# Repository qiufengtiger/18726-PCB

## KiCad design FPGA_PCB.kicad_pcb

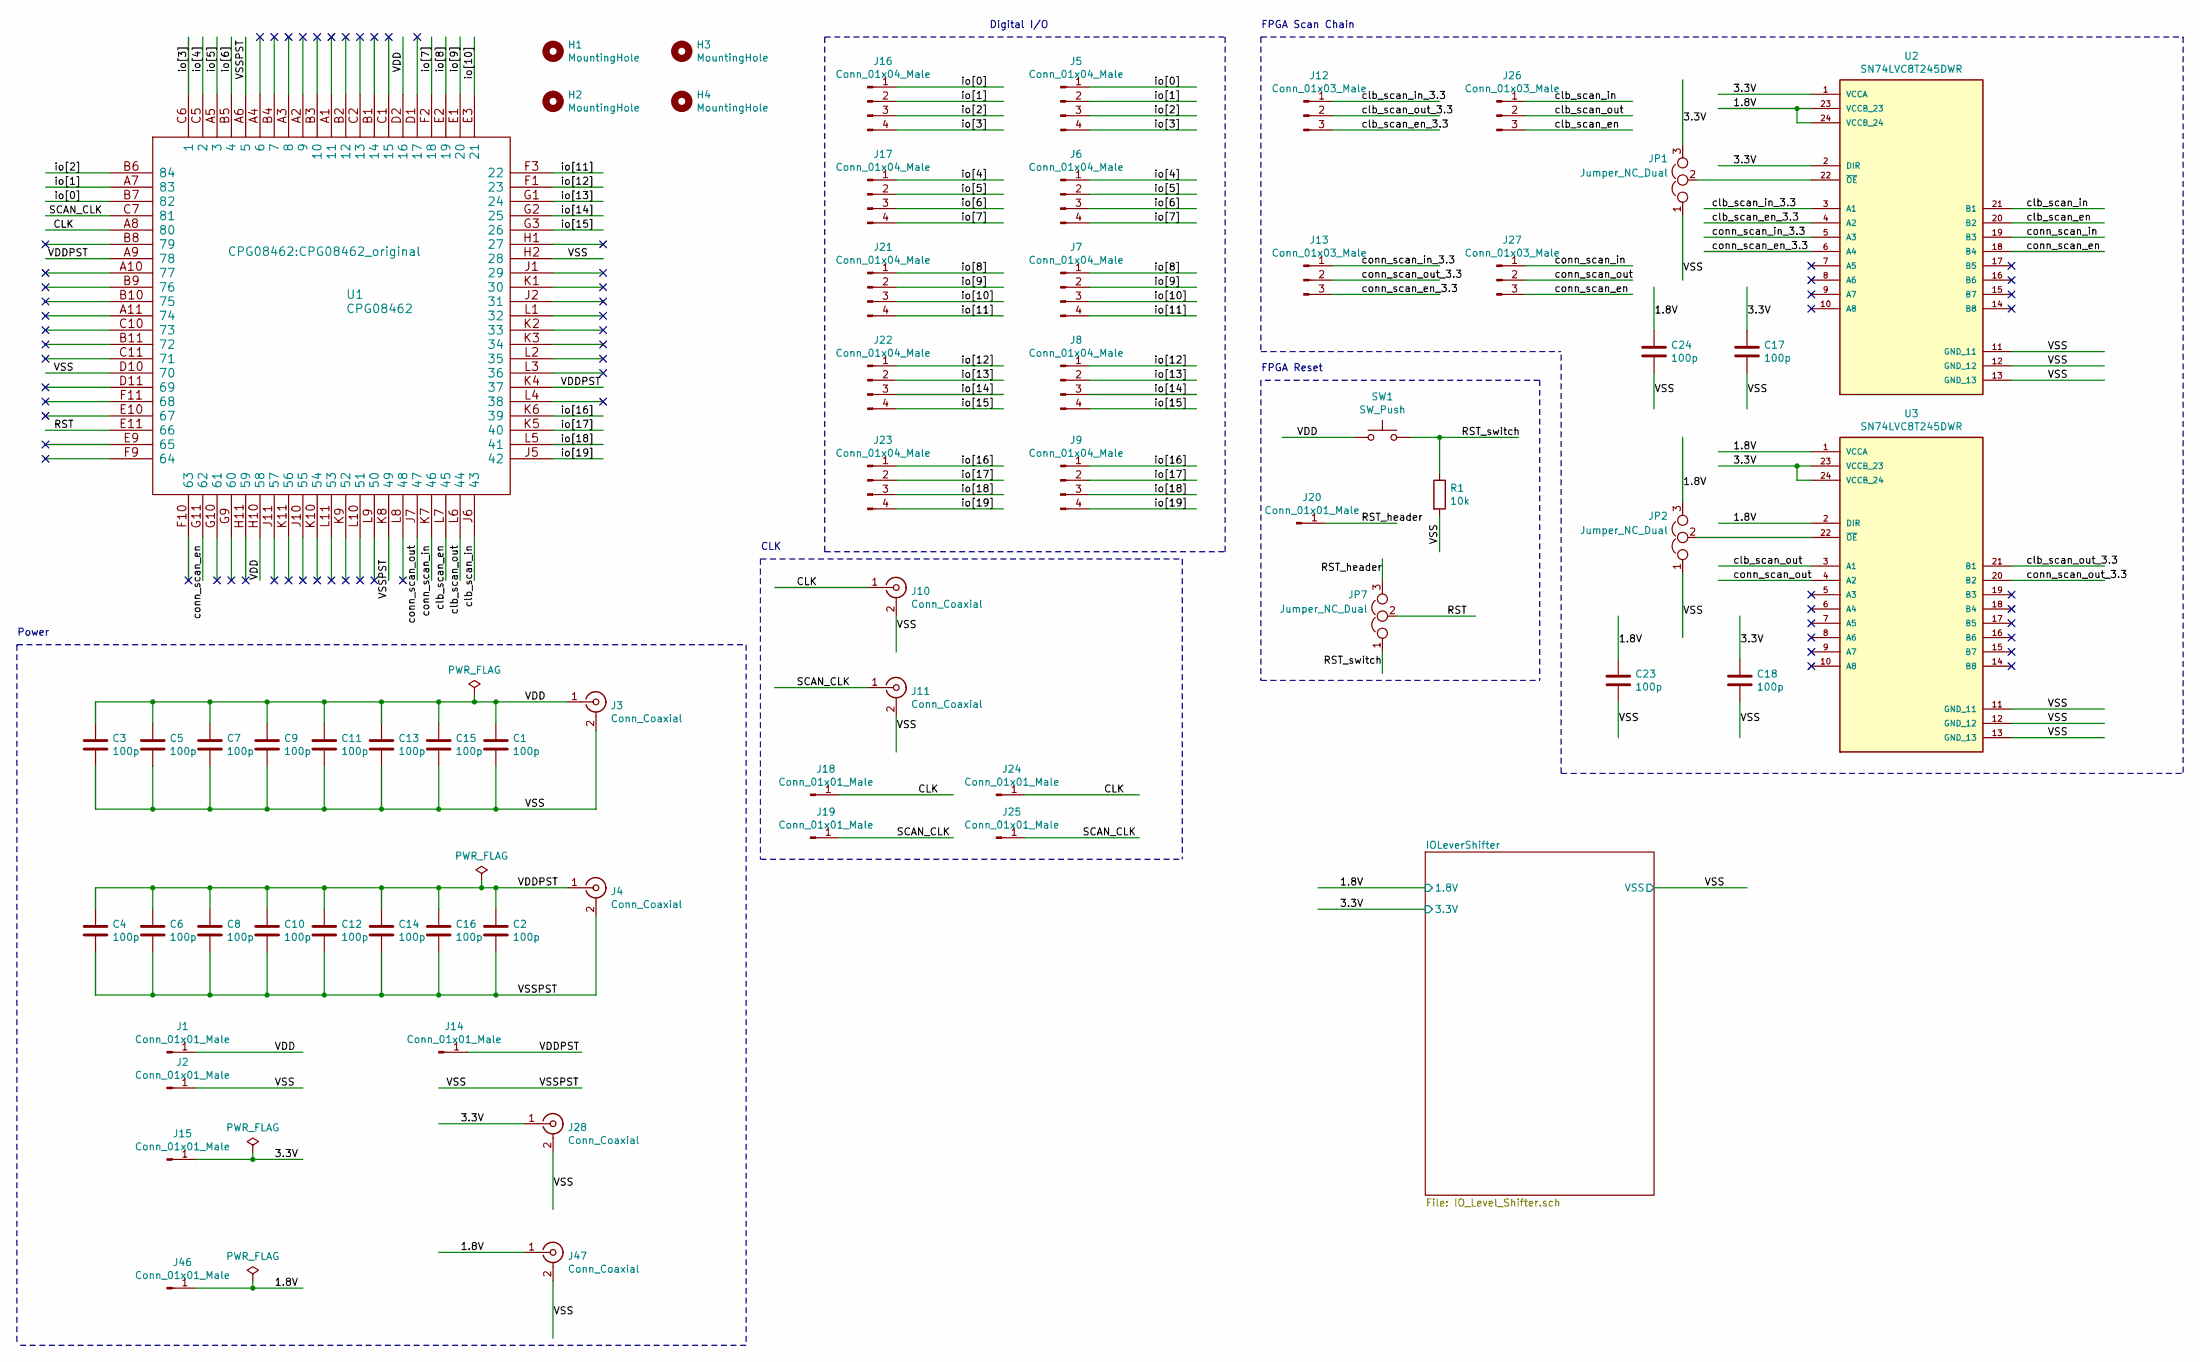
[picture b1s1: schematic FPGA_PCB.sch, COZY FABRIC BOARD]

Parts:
C1, C2, C3, C4, C5, C6, C7, C8, C9, C10, C11, C12, C13, C14, C15, C16, C17, C18, C23, C24: 100p; C_0805_2012Metric_Pad1.15x1.40mm_HandSolder
H1, H2, H3, H4: MountingHole; MountingHole_3.2mm_M3
J1, J2, J14, J15, J18, J19, J20, J24, J25, J46: Conn_01x01_Male; PinHeader_1x01_P2.54mm_Vertical
J3, J4, J10, J11, J28, J47: Conn_Coaxial; BNC_TEConnectivity_1478204_Vertical
J5, J6, J7, J8, J9, J16, J17, J21, J22, J23: Conn_01x04_Male; PinHeader_1x04_P2.54mm_Vertical
J12, J13, J26, J27: Conn_01x03_Male; PinHeader_1x03_P2.54mm_Vertical
JP1, JP2, JP7: Jumper_NC_Dual; PinHeader_1x03_P2.54mm_Vertical
R1: 10k; R_0805_2012Metric_Pad1.15x1.40mm_HandSolder
SW1: SW_Push; SW_SPST_TL3305A
U1: CPG08462; CPG08462_original
U2, U3: SN74LVC8T245DWR; SOIC127P1030X265-24N; PARTREV C

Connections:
/1.8V: C23.1, C24.1, J46.1, J47.1 (In), JP2.3, U2.23 (VCCB_23), U2.24 (VCCB_24), U3.1 (VCCA), U3.2 (DIR); also elsewhere on the board
/3.3V: C17.1, C18.1, J15.1, J28.1 (In), JP1.3, U2.1 (VCCA), U2.2 (DIR), U3.23 (VCCB_23), U3.24 (VCCB_24); also elsewhere on the board
/CLK: J10.1 (In), J18.1, J24.1, U1.A8 (80)
/RST: JP7.2, U1.E11 (66)
/RST_header: J20.1, JP7.3
/RST_switch: JP7.1, R1.1, SW1.2
/SCAN_CLK: J11.1 (In), J19.1, J25.1, U1.C7 (81)
/VDD: C1.1, C3.1, C5.1, C7.1, C9.1, C11.1, C13.1, C15.1, J1.1, J3.1 (In), SW1.1, U1.D2 (16), U1.H10 (58)
/VDDPST: C2.1, C4.1, C6.1, C8.1, C10.1, C12.1, C14.1, C16.1, J4.1 (In), J14.1, U1.A9 (78), U1.K4 (37)
/VSS: C1.2, C2.2, C3.2, C4.2, C5.2, C6.2, C7.2, C8.2, C9.2, C10.2, C11.2, C12.2, C13.2, C14.2, C15.2, C16.2, C17.2, C18.2, C23.2, C24.2, J2.1, J3.2 (Ext), J4.2 (Ext), J10.2 (Ext), J11.2 (Ext), J28.2 (Ext), J47.2 (Ext), JP1.1, JP2.1, R1.2, U1.A6 (5), U1.D10 (70), U1.H2 (28), U1.K8 (49), U2.11 (GND_11), U2.12 (GND_12), U2.13 (GND_13), U3.11 (GND_11), U3.12 (GND_12), U3.13 (GND_13); also elsewhere on the board
/clb_scan_en: J26.3, U1.L7 (45), U2.20 (B2)
/clb_scan_en_3.3: J12.3, U2.4 (A2)
/clb_scan_in: J26.1, U1.J6 (43), U2.21 (B1)
/clb_scan_in_3.3: J12.1, U2.3 (A1)
/clb_scan_out: J26.2, U1.L6 (44), U3.3 (A1)
/clb_scan_out_3.3: J12.2, U3.21 (B1)
/conn_scan_en: J27.3, U1.G11 (62), U2.18 (B4)
/conn_scan_en_3.3: J13.3, U2.6 (A4)
/conn_scan_in: J27.1, U1.K7 (46), U2.19 (B3)
/conn_scan_in_3.3: J13.1, U2.5 (A3)
/conn_scan_out: J27.2, U1.J7 (47), U3.4 (A2)
/conn_scan_out_3.3: J13.2, U3.20 (B2)
/io[0]: J5.1, J16.1, U1.B7 (82)
/io[1]: J5.2, J16.2, U1.A7 (83)
/io[2]: J5.3, J16.3, U1.B6 (84)
/io[3]: J5.4, J16.4, U1.C6 (1)
/io[4]: J6.1, J17.1, U1.C5 (2)
/io[5]: J6.2, J17.2, U1.A5 (3)
/io[6]: J6.3, J17.3, U1.B5 (4)
/io[7]: J6.4, J17.4, U1.F2 (18)
/io[8]: J7.1, J21.1, U1.E2 (19)
/io[9]: J7.2, J21.2, U1.E1 (20)
/io[10]: J7.3, J21.3, U1.E3 (21)
/io[11]: J7.4, J21.4, U1.F3 (22)
/io[12]: J8.1, J22.1, U1.F1 (23)
/io[13]: J8.2, J22.2, U1.G1 (24)
/io[14]: J8.3, J22.3, U1.G2 (25)
/io[15]: J8.4, J22.4, U1.G3 (26)
/io[16]: J9.1, J23.1, U1.K6 (39)
/io[17]: J9.2, J23.2, U1.K5 (40)
/io[18]: J9.3, J23.3, U1.L5 (41)
/io[19]: J9.4, J23.4, U1.J5 (42)
unnamed: JP1.2, U2.22 (~OE)
unnamed: JP2.2, U3.22 (~OE)

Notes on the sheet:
Digital I/O
FPGA Scan Chain
Power
CLK
FPGA Reset

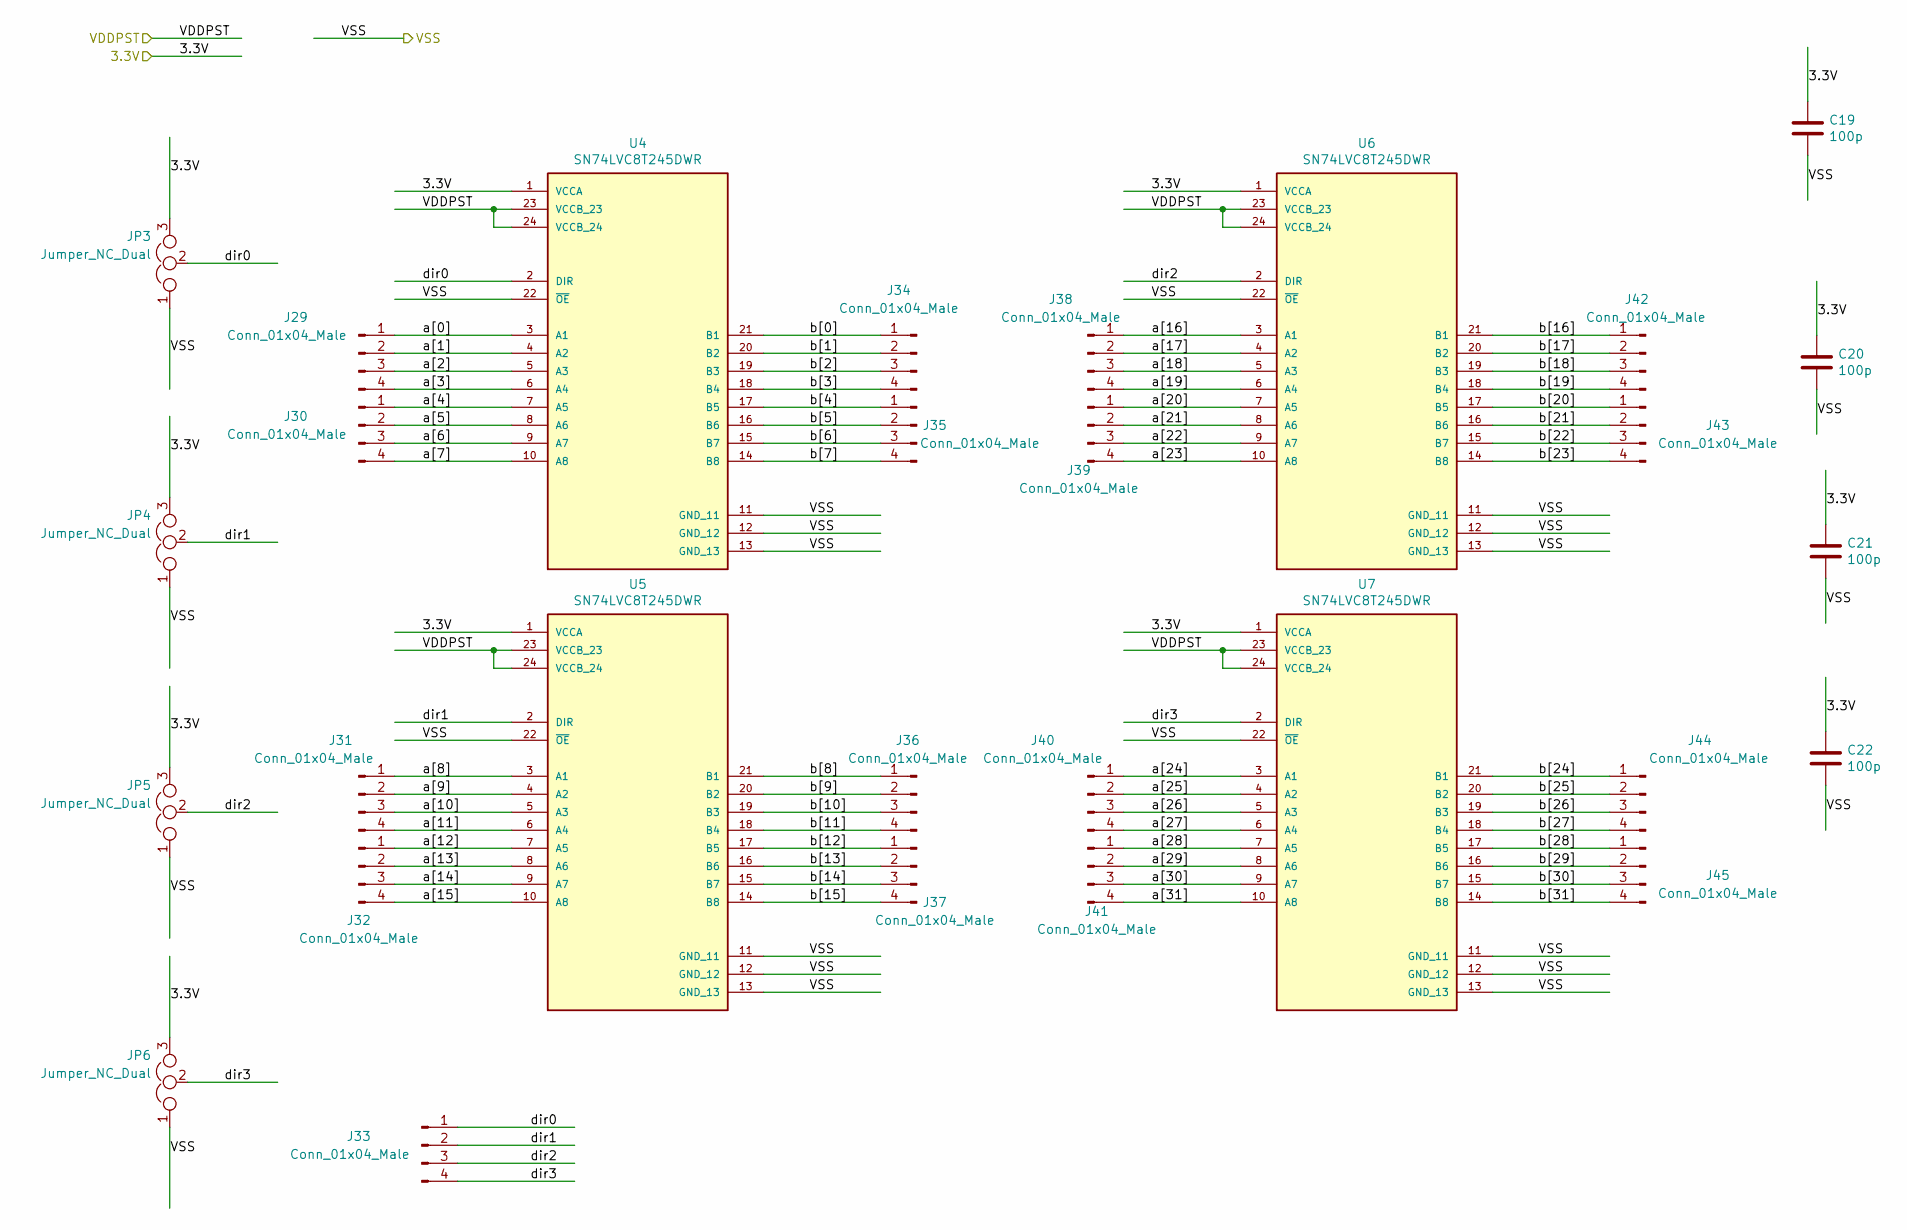
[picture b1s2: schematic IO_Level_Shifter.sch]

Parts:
C19, C20, C21, C22: 100p; C_0805_2012Metric_Pad1.15x1.40mm_HandSolder
J29, J30, J31, J32, J33, J34, J35, J36, J37, J38, J39, J40, J41, J42, J43, J44, J45: Conn_01x04_Male; PinHeader_1x04_P2.54mm_Vertical
JP3, JP4, JP5, JP6: Jumper_NC_Dual; PinHeader_1x03_P2.54mm_Vertical
U4, U5, U6, U7: SN74LVC8T245DWR; SOIC127P1030X265-24N; PARTREV C

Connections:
/1.8V: U4.23 (VCCB_23), U4.24 (VCCB_24), U5.23 (VCCB_23), U5.24 (VCCB_24), U6.23 (VCCB_23), U6.24 (VCCB_24), U7.23 (VCCB_23), U7.24 (VCCB_24); also elsewhere on the board
/3.3V: C19.1, C20.1, C21.1, C22.1, JP3.3, JP4.3, JP5.3, JP6.3, U4.1 (VCCA), U5.1 (VCCA), U6.1 (VCCA), U7.1 (VCCA); also elsewhere on the board
/IOLeverShifter/a[0]: J29.1, U4.3 (A1)
/IOLeverShifter/a[1]: J29.2, U4.4 (A2)
/IOLeverShifter/a[2]: J29.3, U4.5 (A3)
/IOLeverShifter/a[3]: J29.4, U4.6 (A4)
/IOLeverShifter/a[4]: J30.1, U4.7 (A5)
/IOLeverShifter/a[5]: J30.2, U4.8 (A6)
/IOLeverShifter/a[6]: J30.3, U4.9 (A7)
/IOLeverShifter/a[7]: J30.4, U4.10 (A8)
/IOLeverShifter/a[8]: J31.1, U5.3 (A1)
/IOLeverShifter/a[9]: J31.2, U5.4 (A2)
/IOLeverShifter/a[10]: J31.3, U5.5 (A3)
/IOLeverShifter/a[11]: J31.4, U5.6 (A4)
/IOLeverShifter/a[12]: J32.1, U5.7 (A5)
/IOLeverShifter/a[13]: J32.2, U5.8 (A6)
/IOLeverShifter/a[14]: J32.3, U5.9 (A7)
/IOLeverShifter/a[15]: J32.4, U5.10 (A8)
/IOLeverShifter/a[16]: J38.1, U6.3 (A1)
/IOLeverShifter/a[17]: J38.2, U6.4 (A2)
/IOLeverShifter/a[18]: J38.3, U6.5 (A3)
/IOLeverShifter/a[19]: J38.4, U6.6 (A4)
/IOLeverShifter/a[20]: J39.1, U6.7 (A5)
/IOLeverShifter/a[21]: J39.2, U6.8 (A6)
/IOLeverShifter/a[22]: J39.3, U6.9 (A7)
/IOLeverShifter/a[23]: J39.4, U6.10 (A8)
/IOLeverShifter/a[24]: J40.1, U7.3 (A1)
/IOLeverShifter/a[25]: J40.2, U7.4 (A2)
/IOLeverShifter/a[26]: J40.3, U7.5 (A3)
/IOLeverShifter/a[27]: J40.4, U7.6 (A4)
/IOLeverShifter/a[28]: J41.1, U7.7 (A5)
/IOLeverShifter/a[29]: J41.2, U7.8 (A6)
/IOLeverShifter/a[30]: J41.3, U7.9 (A7)
/IOLeverShifter/a[31]: J41.4, U7.10 (A8)
/IOLeverShifter/b[0]: J34.1, U4.21 (B1)
/IOLeverShifter/b[1]: J34.2, U4.20 (B2)
/IOLeverShifter/b[2]: J34.3, U4.19 (B3)
/IOLeverShifter/b[3]: J34.4, U4.18 (B4)
/IOLeverShifter/b[4]: J35.1, U4.17 (B5)
/IOLeverShifter/b[5]: J35.2, U4.16 (B6)
/IOLeverShifter/b[6]: J35.3, U4.15 (B7)
/IOLeverShifter/b[7]: J35.4, U4.14 (B8)
/IOLeverShifter/b[8]: J36.1, U5.21 (B1)
/IOLeverShifter/b[9]: J36.2, U5.20 (B2)
/IOLeverShifter/b[10]: J36.3, U5.19 (B3)
/IOLeverShifter/b[11]: J36.4, U5.18 (B4)
/IOLeverShifter/b[12]: J37.1, U5.17 (B5)
/IOLeverShifter/b[13]: J37.2, U5.16 (B6)
/IOLeverShifter/b[14]: J37.3, U5.15 (B7)
/IOLeverShifter/b[15]: J37.4, U5.14 (B8)
/IOLeverShifter/b[16]: J42.1, U6.21 (B1)
/IOLeverShifter/b[17]: J42.2, U6.20 (B2)
/IOLeverShifter/b[18]: J42.3, U6.19 (B3)
/IOLeverShifter/b[19]: J42.4, U6.18 (B4)
/IOLeverShifter/b[20]: J43.1, U6.17 (B5)
/IOLeverShifter/b[21]: J43.2, U6.16 (B6)
/IOLeverShifter/b[22]: J43.3, U6.15 (B7)
/IOLeverShifter/b[23]: J43.4, U6.14 (B8)
/IOLeverShifter/b[24]: J44.1, U7.21 (B1)
/IOLeverShifter/b[25]: J44.2, U7.20 (B2)
/IOLeverShifter/b[26]: J44.3, U7.19 (B3)
/IOLeverShifter/b[27]: J44.4, U7.18 (B4)
/IOLeverShifter/b[28]: J45.1, U7.17 (B5)
/IOLeverShifter/b[29]: J45.2, U7.16 (B6)
/IOLeverShifter/b[30]: J45.3, U7.15 (B7)
/IOLeverShifter/b[31]: J45.4, U7.14 (B8)
/IOLeverShifter/dir0: J33.1, JP3.2, U4.2 (DIR)
/IOLeverShifter/dir1: J33.2, JP4.2, U5.2 (DIR)
/IOLeverShifter/dir2: J33.3, JP5.2, U6.2 (DIR)
/IOLeverShifter/dir3: J33.4, JP6.2, U7.2 (DIR)
/VSS: C19.2, C20.2, C21.2, C22.2, JP3.1, JP4.1, JP5.1, JP6.1, U4.11 (GND_11), U4.12 (GND_12), U4.13 (GND_13), U4.22 (~OE), U5.11 (GND_11), U5.12 (GND_12), U5.13 (GND_13), U5.22 (~OE), U6.11 (GND_11), U6.12 (GND_12), U6.13 (GND_13), U6.22 (~OE), U7.11 (GND_11), U7.12 (GND_12), U7.13 (GND_13), U7.22 (~OE); also elsewhere on the board

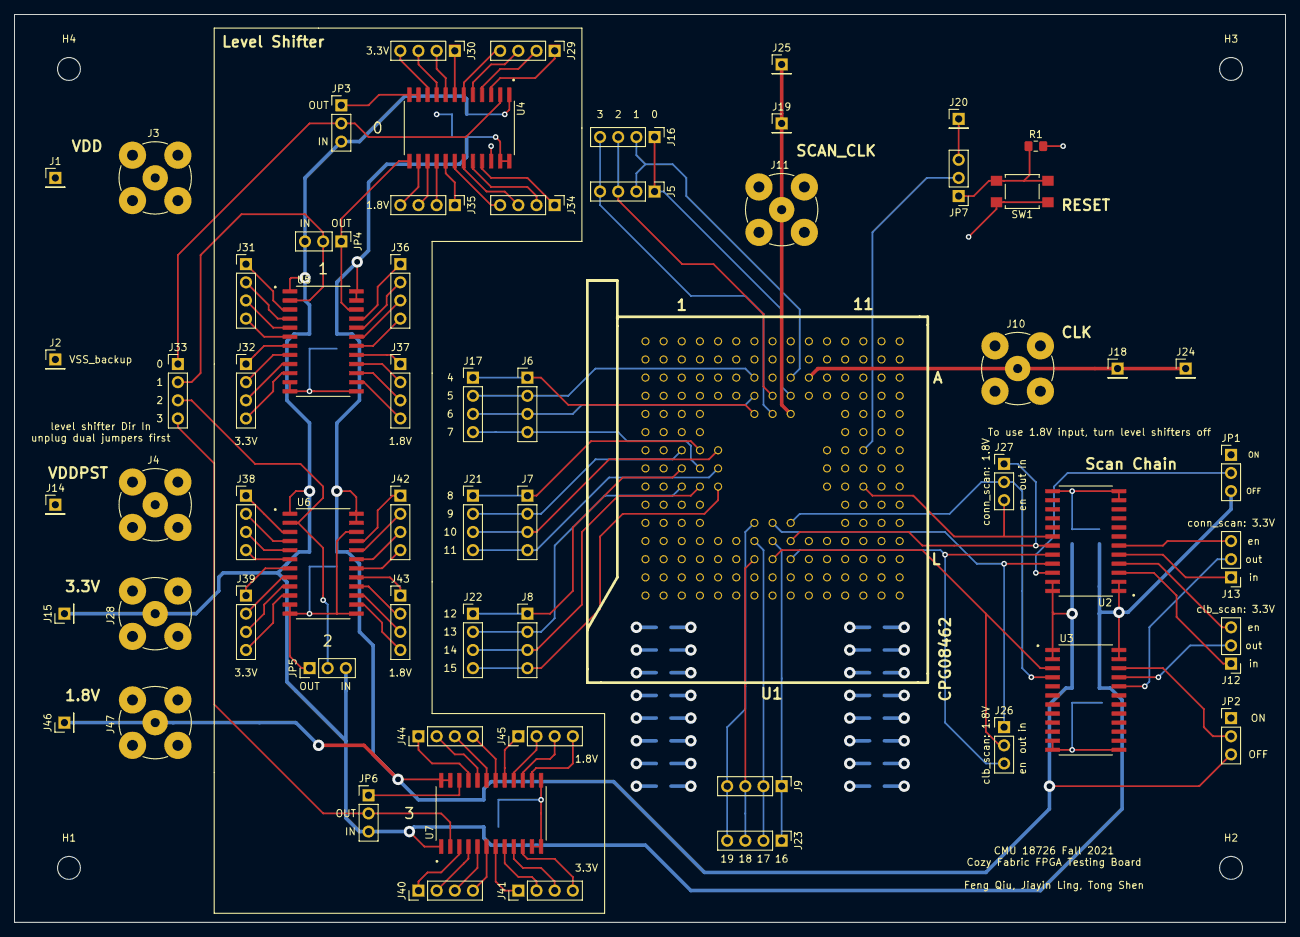
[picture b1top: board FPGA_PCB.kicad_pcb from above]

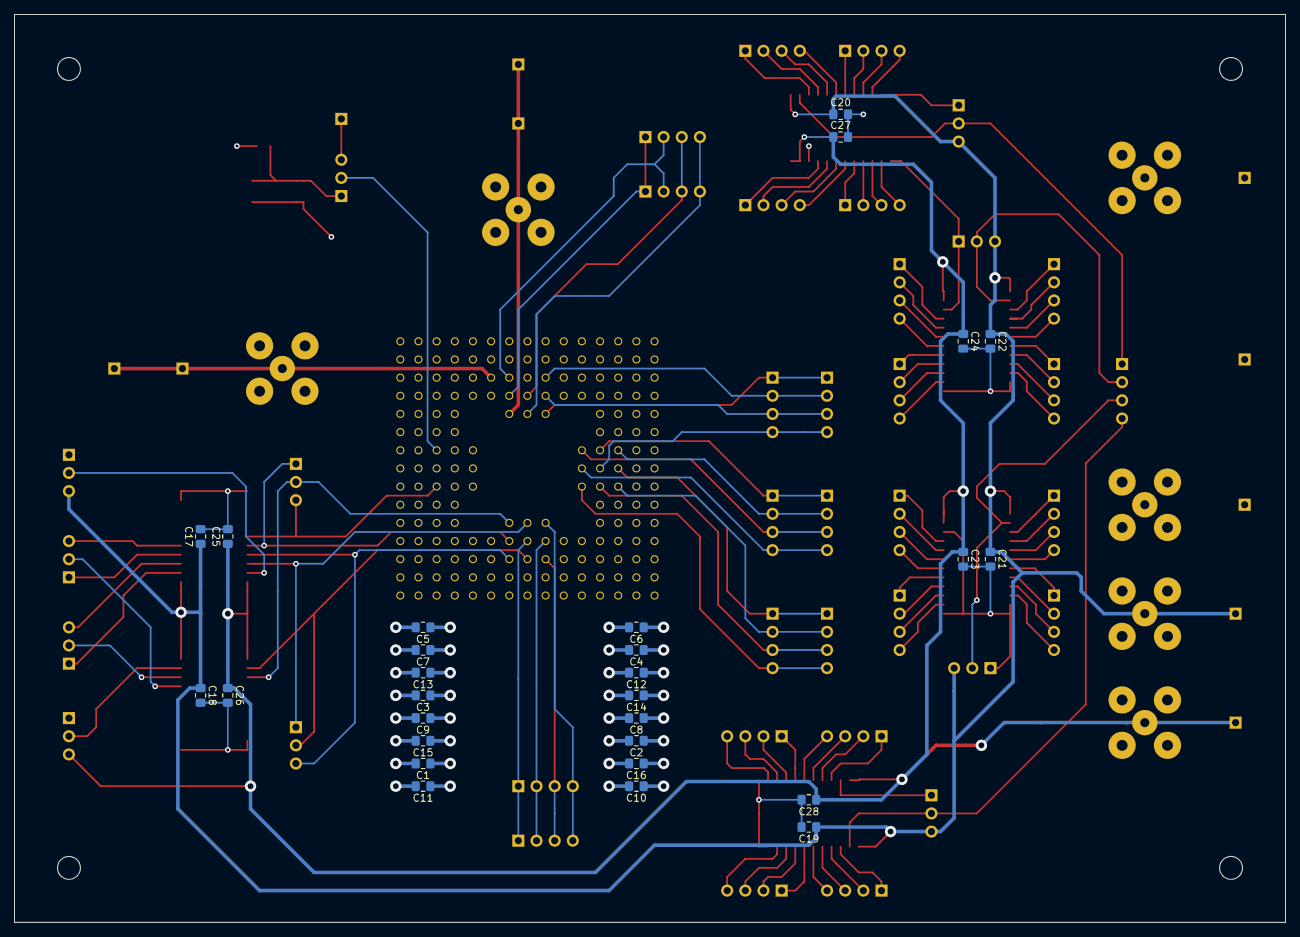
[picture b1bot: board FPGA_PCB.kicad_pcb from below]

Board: 4 copper layers, 177.8 x 127.0 mm, 95 parts (28 on the bottom side), 112 nets.

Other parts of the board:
C25, C26, C27, C28: 100p; C_0805_2012Metric_Pad1.15x1.40mm_HandSolder

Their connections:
/1.8V: C25.1, C26.1, C27.1, C28.1; also elsewhere on the board
/VSS: C25.2, C26.2, C27.2, C28.2; also elsewhere on the board

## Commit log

2021-09-21 PCB schematic
2021-09-23 sch done
2021-09-23 layout done
2021-09-23 layout DRC fixed
2021-09-23 layout fixed fill gap
2021-09-30 ver 2.0
2021-10-01 ver 3.0: added i/o level shifters
2021-10-01 ver 4.0: added 1.8V pin
